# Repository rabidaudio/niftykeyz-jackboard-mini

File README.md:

An alternative jack board for the [Cre8audio NiftyKeyz modular keyboard](https://www.cre8audio.com/niftykeyz).

The original sits too far into the case, taking space away from the modules.
This one shrinks the width as much as possible, and causes the jacks to sit a
few extra millimeters out of the back of the case.

Flat flex connector: [HLW10S-2C7LF](https://www.digikey.com/en/products/detail/amphenol-icc-fci/hlw10s-2c7lf/1002138)

See the blog post: https://rabid.audio/2023/05/28/niftykeyz-mod/

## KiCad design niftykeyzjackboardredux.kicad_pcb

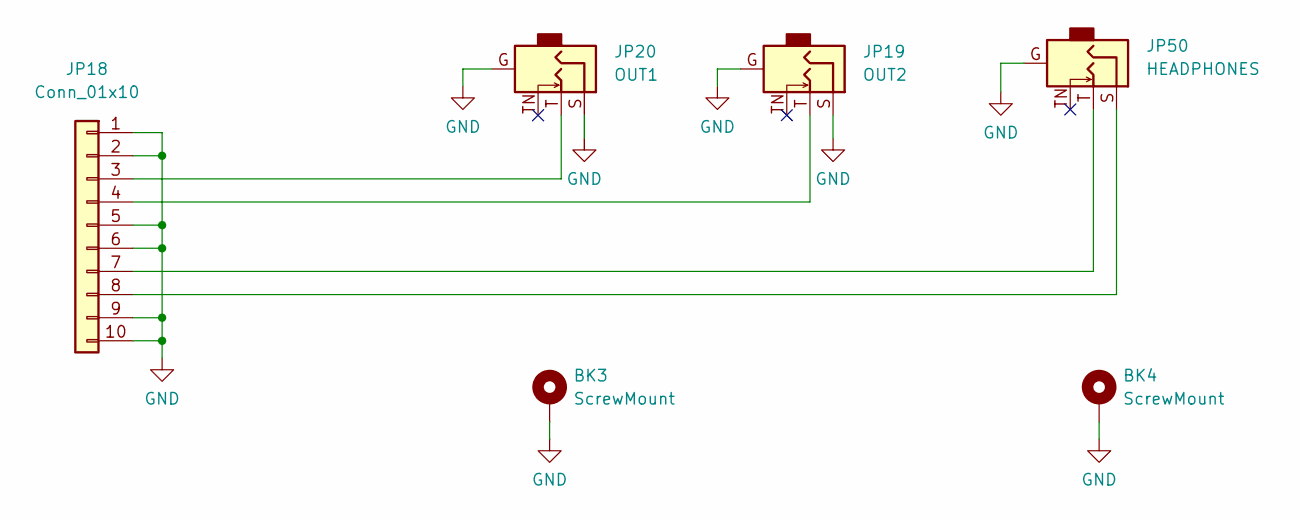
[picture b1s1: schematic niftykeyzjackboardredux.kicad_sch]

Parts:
BK3, BK4: ScrewMount; screw-mount
JP18: Conn_01x10; HLW10S-2C7LF
JP19: OUT2; Jack 6.35mm PJ603
JP20: OUT1; Jack 6.35mm PJ603
JP50: HEADPHONES; Jack 6.35mm PJ603

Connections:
GND: BK3.1, BK4.1, JP18.1, JP18.2, JP18.5, JP18.6, JP18.9, JP18.10, JP19.G, JP19.S, JP20.G, JP20.S, JP50.G
unnamed: JP18.3, JP20.T
unnamed: JP18.4, JP19.T
unnamed: JP18.7, JP50.T
unnamed: JP18.8, JP50.S

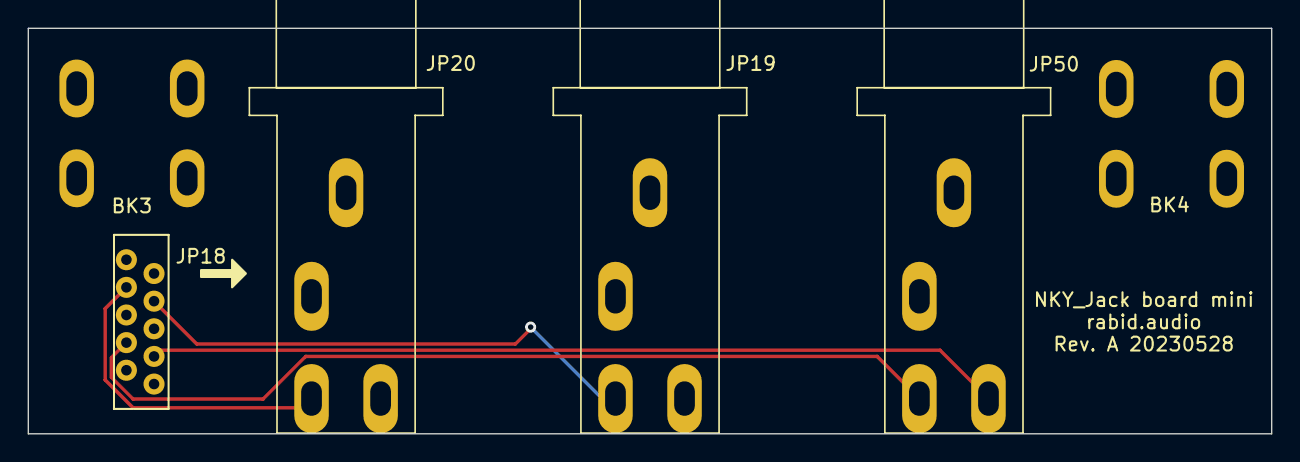
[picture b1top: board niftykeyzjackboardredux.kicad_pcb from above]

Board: 2 copper layers, 90.0 x 29.3 mm, 6 parts (0 on the bottom side), 5 nets.

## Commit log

2023-05-28 adusted stick-out length
2023-05-30 Create LICENSE
2023-05-31 add link to README
2023-06-01 update board
